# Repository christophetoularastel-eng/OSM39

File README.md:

# OSM39

*English version below.*

Un ordinateur 8 bits fait maison autour d'un **Hitachi HD6309** à
1,8432 MHz, avec son système complet : un BIOS de 8 Ko en EPROM, un
bureau graphique en mode texte (OSM-VISION) et des programmes chargés
depuis une carte SD formatée dans un système de fichiers maison (OSMFS).

## Ce qu'il y a dedans

- **128 Ko de RAM** en 4 pages de 32 Ko, **vidéo 80 × 30** caractères
  (68B45, sortie VGA 640 × 480, 8 couleurs, police en EPROM avec une page
  de semi-graphiques), **clavier PS/2**, **carte SD** (SPI matériel),
  **son AY-3-8910** et 6840, **liaison série** 115200 bauds.
- **Logiciel** (tout en assembleur 6309) :
  - le BIOS : démarrage automatique depuis la carte SD, système de
    fichiers OSMFS avec dossiers, console, clavier, son, appels entre pages ;
  - OSM-VISION : gestionnaire de fichiers à fenêtres, menus, Terminal ;
    il se pilote aussi à la « Clouris », une souris tactile à clous ;
  - des applications : EDIT (éditeur façon WordStar), CALC (tableur façon
    VisiCalc), MINITEL (terminal Vidéotex, jusqu'à MiniPavi par un vrai
    modem), PAROLE (synthèse vocale en français), un lecteur de musique
    pour l'AY, et des jeux : GLOUTON, ENVAHIS, BRIQUES, DONJON39 (un
    labyrinthe en 3D) ;
  - un assembleur 6309 qui tourne sur la machine (sa sortie est identique,
    octet pour octet, à celle de lwasm), un FORTH, un SHELL et ses commandes ;
  - des outils PC : préparation de la carte SD (`tools/egofs`), pilotage
    à distance par la liaison série (`tools/tele`), simulations logiques
    des cartes à partir de leurs netlists KiCad.
- **Un manuel de l'utilisateur** : `docs/manuel/` (le PDF est joint aux
  versions publiées, voir « Releases »).

## État du matériel

- **Ce qui tourne aujourd'hui** est la version à plusieurs cartes (carte
  CPU, carte vidéo CRT2, carte SD-clavier-son) : tout le logiciel de ce
  dépôt y est essayé.
- **OSM39_mono** (`materiel/OSM39_mono`) réunit tout sur une seule carte.
  Elle est montée et **fonctionne** depuis le 15 novembre 2026, avec tout
  le logiciel (VRAM entrelacée : construire avec `mono` dans le fichier
  `CARTE`). **Deux corrections** sont nécessaires sur la carte : elles sont
  dans le schéma, mais **le circuit imprimé n'est pas encore repris** ; sur
  une carte faite avec le circuit imprimé actuel, il faut les câbler :
  1. qualifier `/8000-9FFF` par E : la porte libre U103 (74HC32, broches
     9-10 -> 8) fait « sortie de U106 (broche 4) OU ~E (U101 broche 10) »,
     et sa sortie remplace celle de U106 vers U501 (1, 2) et U517 (2, 4, 9) ;
     sans elle, de la neige dès qu'un programme tourne en RAM basse ;
  2. relier l'OE (broche 22) de l'EPROM de police U515 à la masse ; sans
     elle, les couleurs sont en avance d'une case.

## Construire le logiciel

Il faut **lwtools 4.24** (`lwasm`, `lwlink`), `objcopy` et `python3`.

```sh
make                 # BIOS, SHELL, FORTH, commandes, ASM, OSM-VISION
./deploy_sd.sh       # tout construire et vérifier, remplir dist/
```

`dist/EPROM/` contient l'image du BIOS (`osm39.bin`, 8 Ko) et la police
(`font_osm39.bin`) à graver ; `dist/SD/` et `dist/DEPLOY.md` décrivent la
carte SD. Pour l'écrire (sur une image de test d'abord, jamais sur le
mauvais périphérique !) :

```sh
python3 tools/egofs/egofs_deploy.py /dev/sdX
```

Au démarrage, le BIOS joue un petit air, affiche sa bannière et charge
OSM-VISION ; une touche dans la première seconde ouvre le moniteur de
secours (chargement Intel hex par la liaison série).

## Les vérificateurs

Le dossier `test/` contient des vérificateurs qui font tourner les vrais
binaires dans un émulateur 6309 (avec la carte SD, le clavier, l'AY... en
modèles) et les comparent à des modèles exacts en Python :

```sh
make -C test bureau      # OSM-VISION au clavier et à la Clouris
make -C test donjon39    # le rendu 3D comparé au modèle
make -C test minitel     # le décodeur Vidéotex et le protocole PCE
```

`AGENTS.md` est la documentation technique de référence (en anglais), et
`docs/memory-map.md` la carte mémoire.

## Ce qui n'est pas ici

- **BBC BASIC** : la machine fait tourner le portage 6809/6309 de BBC BASIC
  IV par Dominic Beesley (<https://github.com/dominicbeesley/beeb6809>).
  Ce dépôt amont n'a pas de licence : ni lui ni la couche d'adaptation
  d'OSM39 ne sont publiés ici. Le manuel en parle quand même.
- Le BASIC d'origine Microsoft (« basic69 ») non plus.
- Les modèles 3D des connecteurs et de l'alimentation (`.STEP`) : ils se
  téléchargent chez les fabricants (Amphenol 86093487313H55ELF, Amphenol
  L77HDE15SD1CH4FVGA, Recom RAC20-05SK).

## Licences

- Matériel (`materiel/`) : **CERN-OHL-S v2** (`materiel/LICENSE`).
- Logiciel : **GPL v3 ou ultérieure** (`LICENSE`).
- Manuel et documentation : **CC BY-SA 4.0** (`docs/LICENSE`).
- `tools/manuel/polices/` : les polices gardent leur licence (SIL OFL).

## Crédits

- Les captures de pages Vidéotex de `tools/minitel/*.vdt`, qui servent aux
  vérificateurs, viennent du serveur **MiniPavi** (`go.minipavi.fr`).

---

# OSM39 (English)

A home-made 8-bit computer built around a **Hitachi HD6309** at
1.8432 MHz, with its whole system: an 8 KB EPROM BIOS, a text-mode
windowed desktop (OSM-VISION) and programs loaded from an SD card
formatted with a home-made file system (OSMFS). Comments, messages and
the user manual are in French.

- **Hardware**: 128 KB RAM in four 32 KB pages, 80 × 30 text video
  (68B45, VGA output, 8 colours, EPROM font with a semigraphics page),
  PS/2 keyboard, SD card on hardware SPI, AY-3-8910 and 6840 sound,
  115200 baud serial line.
- **Software** (6309 assembly): BIOS with auto-boot and a file system
  with folders; OSM-VISION file manager; an editor, a spreadsheet, a
  Videotex terminal, French text-to-speech, an AY music player, games; a
  native 6309 assembler (byte-identical to lwasm), FORTH, a shell; PC
  tools to build the SD card, drive the machine over the serial line and
  simulate the boards from their KiCad netlists.
- **Status**: the software runs on the multi-board machine (CPU, CRT2
  video, SD-keyboard-sound) and, since 2026-11-15, on **OSM39_mono**, the
  single-board version in `materiel/OSM39_mono` (build with `mono` in the
  `CARTE` file). Two fixes are in its schematic but **not yet in the PCB**:
  wire them on a board made from the current PCB (qualify `/8000-9FFF`
  with E through the spare U103 gate; tie the font EEPROM U515 OE to
  ground). Details above, in French.
- **Build**: lwtools 4.24, `objcopy`, `python3`; `make`, then
  `./deploy_sd.sh` fills `dist/` (EPROM images, SD card contents).
  `make -C test <name>` runs the verifiers (real binaries in a 6309
  emulator, compared with exact Python models).
- **Not included**: BBC BASIC (Dominic Beesley's 6809 port has no
  licence) and the Microsoft-derived BASIC; vendor 3D models.
- **Licences**: hardware CERN-OHL-S v2, software GPL v3 or later,
  documentation CC BY-SA 4.0.

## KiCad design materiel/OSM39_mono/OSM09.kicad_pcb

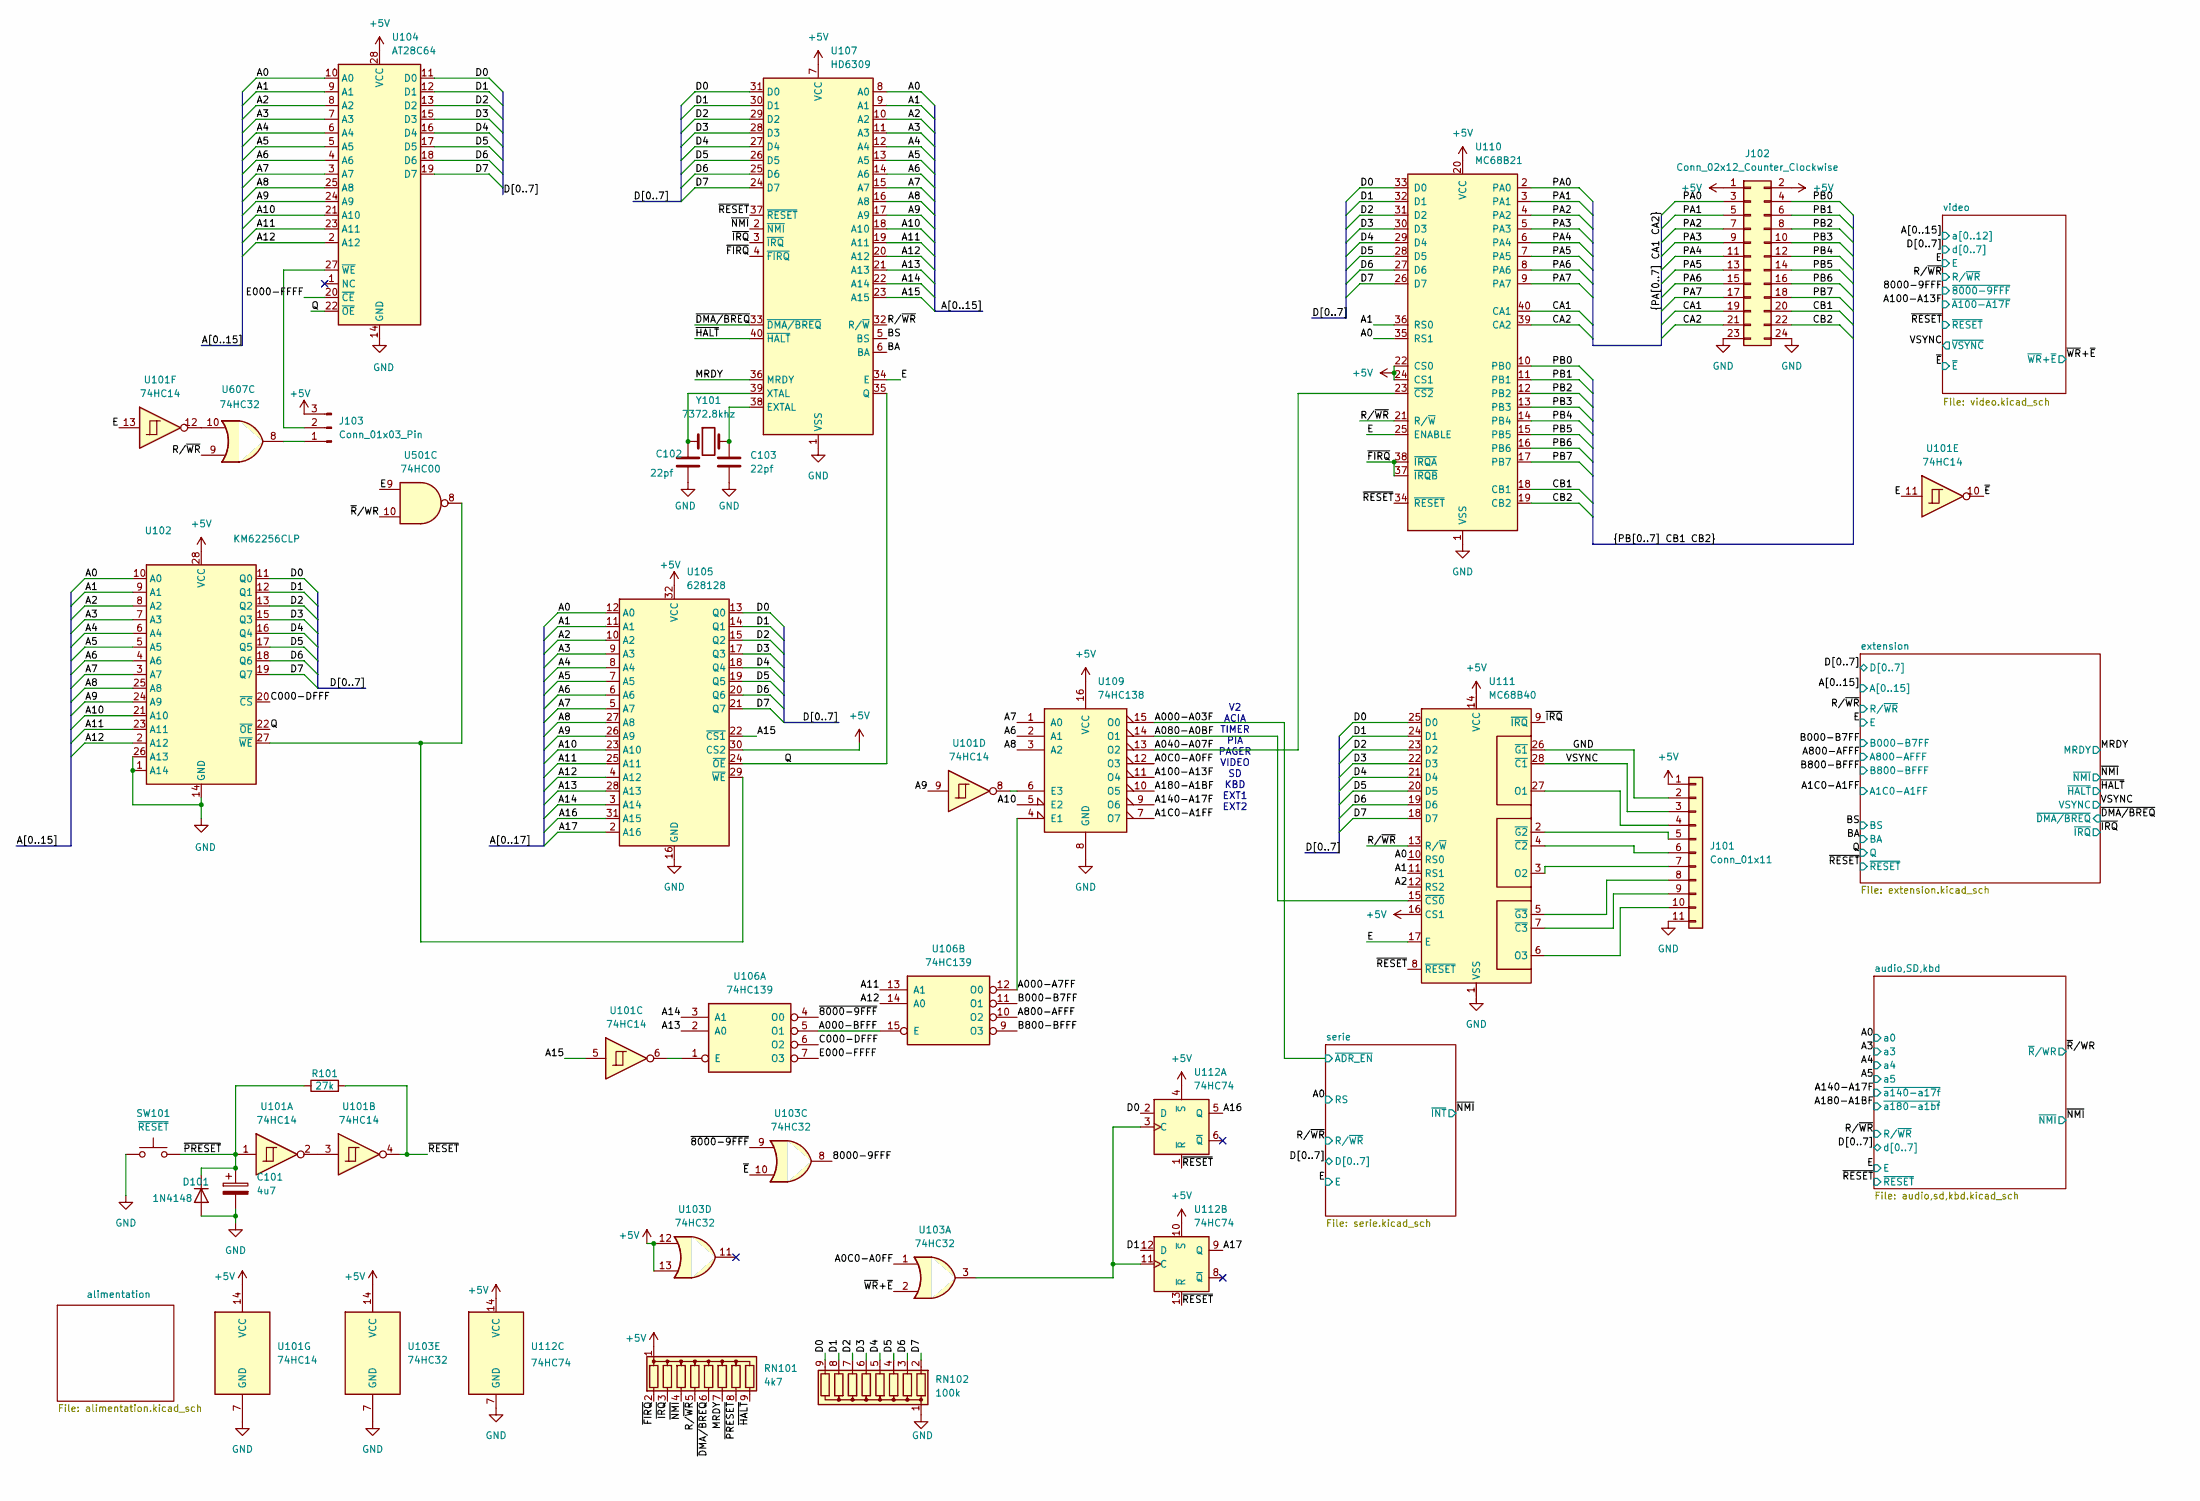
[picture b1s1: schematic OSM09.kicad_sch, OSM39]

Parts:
C101: 4u7; CP_Radial_D4.0mm_P1.50mm
C102, C103: 22pf; C_Disc_D5.0mm_W2.5mm_P2.50mm
D101: 1N4148; D_DO-35_SOD27_P7.62mm_Horizontal
J101: Conn_01x11; PinHeader_1x11_P2.54mm_Vertical
J102: Conn_02x12_Counter_Clockwise; PinHeader_2x12_P2.54mm_Vertical
J103: Conn_01x03_Pin; PinHeader_1x03_P2.54mm_Vertical
R101: 27k; R_Axial_DIN0204_L3.6mm_D1.6mm_P7.62mm_Horizontal
RN101: 4k7; R_Array_SIP9
RN102: 100k; R_Array_SIP9
SW101: ~{RESET}; SW_PUSH_6mm
U101: 74HC14; DIP-14_W7.62mm_LongPads
U102: KM62256CLP; DIP-28_W15.24mm_LongPads
U103, U607: 74HC32; DIP-14_W7.62mm_LongPads
U104: AT28C64; DIP-28_W15.24mm_LongPads
U105: 628128; DIP-32_W15.24mm_LongPads
U106: 74HC139; DIP-16_W7.62mm_LongPads
U107: HD6309; DIP-40_W15.24mm_LongPads
U109: 74HC138; DIP-16_W7.62mm_LongPads
U110: MC68B21; DIP-40_W15.24mm_LongPads
U111: MC68B40; DIP-28_W15.24mm_LongPads
U112: 74HC74; DIP-14_W7.62mm_LongPads
U501: 74HC00; DIP-14_W7.62mm_LongPads
Y101: 7372.8khz; Crystal_HC49-U_Vertical

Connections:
+5V: J101.1, J102.1, J102.2, J103.3, RN101.1 (common), U101.14 (VCC), U102.28 (VCC), U103.12, U103.13, U103.14 (VCC), U104.28 (VCC), U105.30 (CS2), U105.32 (VCC), U107.7 (VCC), U109.16 (VCC), U110.20 (VCC), U110.22 (CS0), U110.24 (CS1), U111.14 (VCC), U111.16 (CS1), U112.4 (~S), U112.10 (~S), U112.14 (VCC); also elsewhere on the board
/8000-9FFF: U103.8; also elsewhere on the board
/A0: U102.10 (A0), U104.10 (A0), U105.12 (A0), U107.8 (A0), U110.35 (RS1), U111.10 (RS0); also elsewhere on the board
/A000-A03F: U109.15 (O0); also elsewhere on the board
/A000-A7FF: U106.12 (O0), U109.4 (E1)
/A000-BFFF: U106.5 (O1), U106.15 (E)
/A0C0-A0FF: U103.1, U109.12 (O3)
/A1: U102.9 (A1), U104.9 (A1), U105.11 (A1), U107.9 (A1), U110.36 (RS0), U111.11 (RS1); also elsewhere on the board
/A1C0-A1FF: U109.7 (O7); also elsewhere on the board
/A2: U102.8 (A2), U104.8 (A2), U105.10 (A2), U107.10 (A2), U111.12 (RS2); also elsewhere on the board
/A3: U102.7 (A3), U104.7 (A3), U105.9 (A3), U107.11 (A3); also elsewhere on the board
/A4: U102.6 (A4), U104.6 (A4), U105.8 (A4), U107.12 (A4); also elsewhere on the board
/A5: U102.5 (A5), U104.5 (A5), U105.7 (A5), U107.13 (A5); also elsewhere on the board
/A6: U102.4 (A6), U104.4 (A6), U105.6 (A6), U107.14 (A6), U109.2 (A1); also elsewhere on the board
/A7: U102.3 (A7), U104.3 (A7), U105.5 (A7), U107.15 (A7), U109.1 (A0); also elsewhere on the board
/A8: U102.25 (A8), U104.25 (A8), U105.27 (A8), U107.16 (A8), U109.3 (A2); also elsewhere on the board
/A9: U101.9, U102.24 (A9), U104.24 (A9), U105.26 (A9), U107.17 (A9); also elsewhere on the board
/A10: U102.21 (A10), U104.21 (A10), U105.23 (A10), U107.18 (A10), U109.5 (E2); also elsewhere on the board
/A11: U102.23 (A11), U104.23 (A11), U105.25 (A11), U106.13 (A1), U107.19 (A11); also elsewhere on the board
/A12: U102.2 (A12), U104.2 (A12), U105.4 (A12), U106.14 (A0), U107.20 (A12); also elsewhere on the board
/A13: U105.28 (A13), U106.2 (A0), U107.21 (A13)
/A14: U105.3 (A14), U106.3 (A1), U107.22 (A14)
/A15: U101.5, U105.22 (~CS1), U107.23 (A15)
/A16: U105.31 (A15), U112.5 (Q)
/A17: U105.2 (A16), U112.9 (Q)
/A040-A07F: U109.13 (O2), U110.23 (~CS2)
/A080-A0BF: U109.14 (O1), U111.15 (~CS0)
/A100-A13F: U109.11 (O4); also elsewhere on the board
/A140-A17F: U109.9 (O6); also elsewhere on the board
/A180-A1BF: U109.10 (O5); also elsewhere on the board
/A800-AFFF: U106.10 (O2); also elsewhere on the board
/B000-B7FF: U106.11 (O1); also elsewhere on the board
/B800-BFFF: U106.9 (O3); also elsewhere on the board
/BA: U107.6 (BA); also elsewhere on the board
/BS: U107.5 (BS); also elsewhere on the board
/C000-DFFF: U102.20 (~CS), U106.6 (O2)
/CA1: J102.19, U110.40 (CA1)
/CA2: J102.21, U110.39 (CA2)
/CB1: J102.20, U110.18 (CB1)
/CB2: J102.22, U110.19 (CB2)
/D0: RN102.9 (R8), U102.11 (Q0), U104.11 (D0), U105.13 (Q0), U107.31 (D0), U110.33 (D0), U111.25 (D0), U112.2 (D); also elsewhere on the board
/D1: RN102.8 (R7), U102.12 (Q1), U104.12 (D1), U105.14 (Q1), U107.30 (D1), U110.32 (D1), U111.24 (D1), U112.12 (D); also elsewhere on the board
/D2: RN102.7 (R6), U102.13 (Q2), U104.13 (D2), U105.15 (Q2), U107.29 (D2), U110.31 (D2), U111.23 (D2); also elsewhere on the board
/D3: RN102.6 (R5), U102.15 (Q3), U104.15 (D3), U105.17 (Q3), U107.28 (D3), U110.30 (D3), U111.22 (D3); also elsewhere on the board
/D4: RN102.5 (R4), U102.16 (Q4), U104.16 (D4), U105.18 (Q4), U107.27 (D4), U110.29 (D4), U111.21 (D4); also elsewhere on the board
/D5: RN102.4 (R3), U102.17 (Q5), U104.17 (D5), U105.19 (Q5), U107.26 (D5), U110.28 (D5), U111.20 (D5); also elsewhere on the board
/D6: RN102.3 (R2), U102.18 (Q6), U104.18 (D6), U105.20 (Q6), U107.25 (D6), U110.27 (D6), U111.19 (D6); also elsewhere on the board
/D7: RN102.2 (R1), U102.19 (Q7), U104.19 (D7), U105.21 (Q7), U107.24 (D7), U110.26 (D7), U111.18 (D7); also elsewhere on the board
/E: U101.11, U101.13, U107.34 (E), U110.25 (ENABLE), U111.17 (E), U501.9; also elsewhere on the board
/E000-FFFF: U104.20 (~CE), U106.7 (O3)
/MRDY: RN101.7 (R6), U107.36 (MRDY); also elsewhere on the board
/PA0: J102.3, U110.2 (PA0)
/PA1: J102.5, U110.3 (PA1)
/PA2: J102.7, U110.4 (PA2)
/PA3: J102.9, U110.5 (PA3)
/PA4: J102.11, U110.6 (PA4)
/PA5: J102.13, U110.7 (PA5)
/PA6: J102.15, U110.8 (PA6)
/PA7: J102.17, U110.9 (PA7)
/PB0: J102.4, U110.10 (PB0)
/PB1: J102.6, U110.11 (PB1)
/PB2: J102.8, U110.12 (PB2)
/PB3: J102.10, U110.13 (PB3)
/PB4: J102.12, U110.14 (PB4)
/PB5: J102.14, U110.15 (PB5)
/PB6: J102.16, U110.16 (PB6)
/PB7: J102.18, U110.17 (PB7)
/Q: U102.22 (~OE), U104.22 (~OE), U105.24 (~OE), U107.35 (Q); also elsewhere on the board
/R/~WR: RN101.5 (R4), U107.32 (R/~W), U110.21 (R/~W), U111.13 (R/~W), U607.9; also elsewhere on the board
/VSYNC: J101.3, U111.28 (~C1); also elsewhere on the board
/~8000-9FFF: U103.9, U106.4 (O0)
/~DMA/BREQ: RN101.6 (R5), U107.33 (~DMA/BREQ); also elsewhere on the board
/~E: U101.10, U103.10; also elsewhere on the board
/~FIRQ: RN101.2 (R1), U107.4 (~FIRQ), U110.37 (~IRQB), U110.38 (~IRQA)
/~HALT: RN101.9 (R8), U107.40 (~HALT); also elsewhere on the board
/~IRQ: RN101.3 (R2), U107.3 (~IRQ), U111.9 (~IRQ); also elsewhere on the board
/~NMI: RN101.4 (R3), U107.2 (~NMI); also elsewhere on the board
/~PRESET: C101.1, D101.1 (K), R101.1, RN101.8 (R7), SW101.2, U101.1
/~RESET: R101.2, U101.4, U107.37 (~RESET), U110.34 (~RESET), U111.8 (~RESET), U112.1 (~R), U112.13 (~R); also elsewhere on the board
/~R/WR: U501.10; also elsewhere on the board
/~WR+~E: U103.2; also elsewhere on the board
GND: C101.2, C102.2, C103.2, D101.2 (A), J101.2, J101.11, J102.23, J102.24, RN102.1 (common), SW101.1, U101.7 (GND), U102.1 (A14), U102.14 (GND), U102.26 (A13), U103.7 (GND), U104.14 (GND), U105.16 (GND), U107.1 (VSS), U109.8 (GND), U110.1 (VSS), U111.1 (VSS), U111.26 (~G1), U112.7 (GND); also elsewhere on the board
unnamed: J101.4, U111.27 (O1)
unnamed: J101.5, U111.2 (~G2)
unnamed: J101.6, U111.4 (~C2)
unnamed: J101.7, U111.3 (O2)
unnamed: J101.8, U111.5 (~G3)
unnamed: J101.9, U111.7 (~C3)
unnamed: J101.10, U111.6 (O3)
unnamed: J103.1, U607.8
unnamed: J103.2, U104.27 (~WE)
unnamed: U101.2, U101.3
unnamed: U101.12, U607.10
unnamed: U102.27 (~WE), U105.29 (~WE), U501.8
unnamed: U101.6, U106.1 (E)
unnamed: C103.1, U107.38 (EXTAL), Y101.2
unnamed: C102.1, U107.39 (XTAL), Y101.1
unnamed: U101.8, U109.6 (E3)
unnamed: U103.3, U112.3 (C), U112.11 (C)

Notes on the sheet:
V2 ACIA TIMER PIA PAGER VIDEO SD KBD EXT1 EXT2

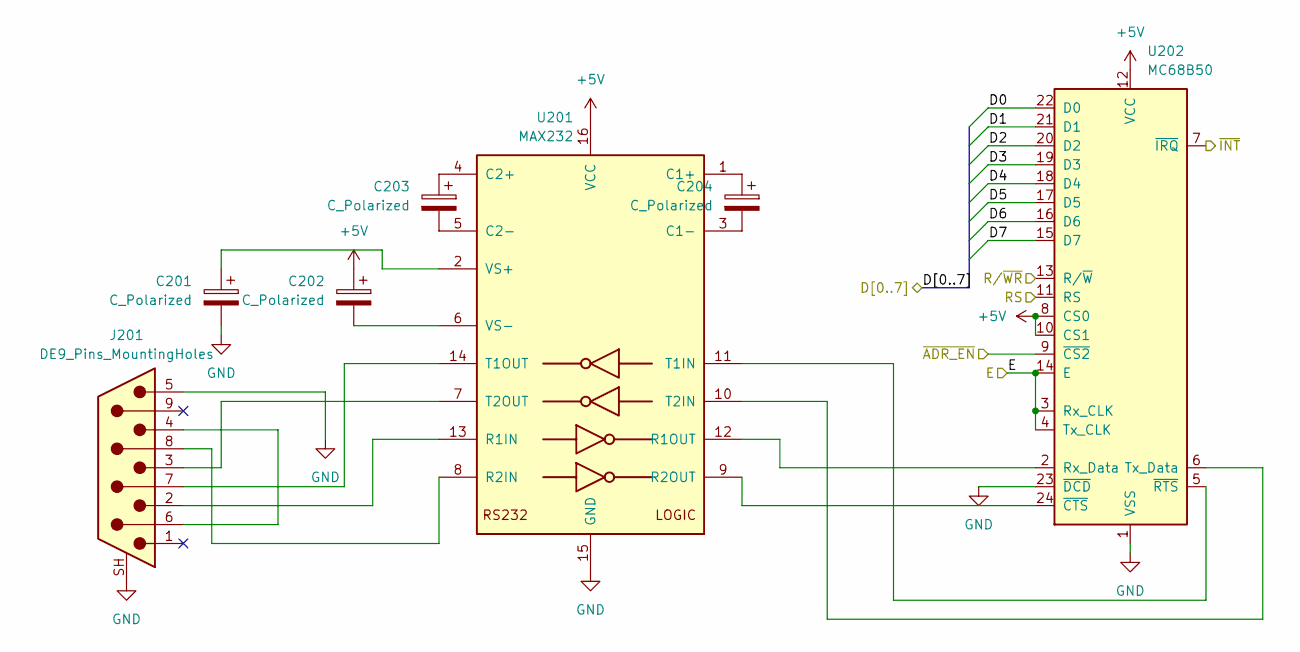
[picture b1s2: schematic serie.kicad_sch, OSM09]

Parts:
C201, C202, C203, C204: C_Polarized; CP_Radial_D4.0mm_P1.50mm
J201: DE9_Pins_MountingHoles; DSUB-9_Pins_Horizontal_P2.77x2.84mm_EdgePinOffset4.94mm_Hou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
U201: MAX232; DIP-16_W7.62mm_LongPads
U202: MC68B50; DIP-24_W15.24mm_LongPads

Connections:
+5V: C202.1, U201.16 (VCC), U202.8 (CS0), U202.10 (CS1), U202.12 (VCC); also elsewhere on the board
/A0: U202.11 (RS); also elsewhere on the board
/A000-A03F: U202.9 (~CS2); also elsewhere on the board
/D0: U202.22 (D0); also elsewhere on the board
/D1: U202.21 (D1); also elsewhere on the board
/D2: U202.20 (D2); also elsewhere on the board
/D3: U202.19 (D3); also elsewhere on the board
/D4: U202.18 (D4); also elsewhere on the board
/D5: U202.17 (D5); also elsewhere on the board
/D6: U202.16 (D6); also elsewhere on the board
/D7: U202.15 (D7); also elsewhere on the board
/E: U202.3 (Rx_CLK), U202.4 (Tx_CLK), U202.14 (E); also elsewhere on the board
/R/~WR: U202.13 (R/~W); also elsewhere on the board
/~NMI: U202.7 (~IRQ); also elsewhere on the board
GND: C201.2, J201.5, J201.SH (PAD), U201.15 (GND), U202.1 (VSS), U202.23 (~DCD); also elsewhere on the board
unnamed: J201.4, J201.6
unnamed: C204.1, U201.1 (C1+)
unnamed: C204.2, U201.3 (C1-)
unnamed: C203.1, U201.4 (C2+)
unnamed: C203.2, U201.5 (C2-)
unnamed: J201.2, U201.13 (R1IN)
unnamed: U201.12 (R1OUT), U202.2 (Rx_Data)
unnamed: J201.8, U201.8 (R2IN)
unnamed: U201.9 (R2OUT), U202.24 (~CTS)
unnamed: U201.11 (T1IN), U202.5 (~RTS)
unnamed: J201.7, U201.14 (T1OUT)
unnamed: U201.10 (T2IN), U202.6 (Tx_Data)
unnamed: J201.3, U201.7 (T2OUT)
unnamed: C201.1, U201.2 (VS+)
unnamed: C202.2, U201.6 (VS-)

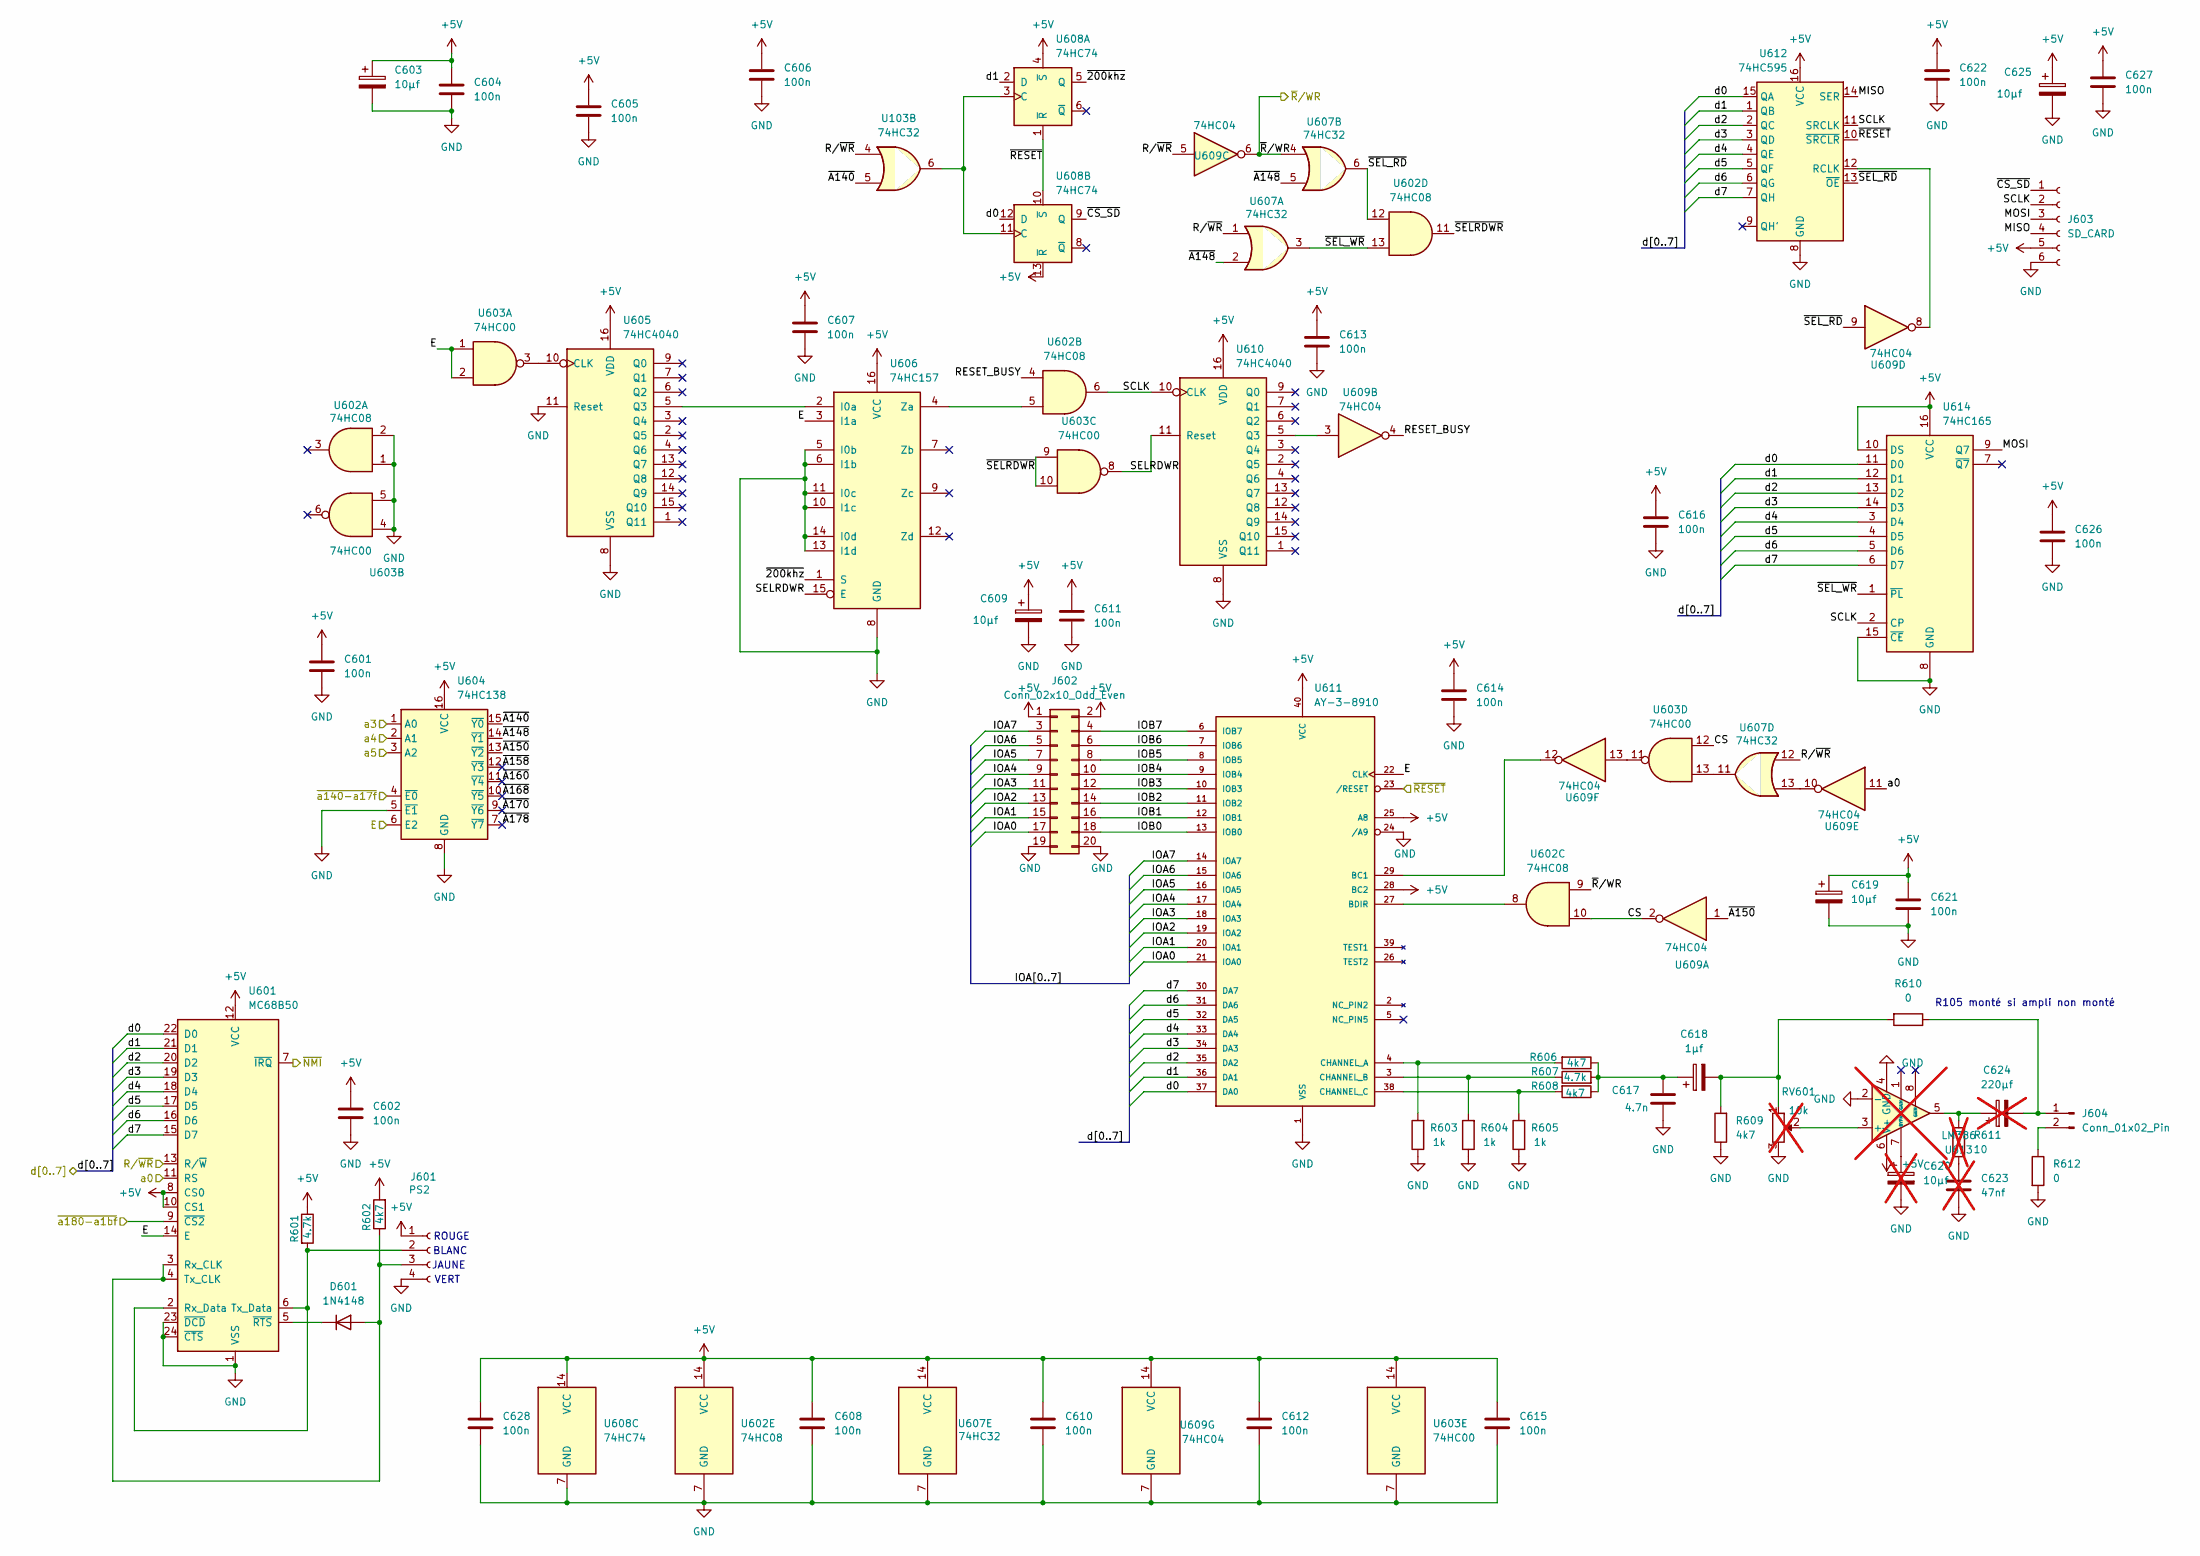
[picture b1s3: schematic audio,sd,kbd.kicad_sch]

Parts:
C601, C602, C604, C605, C606, C607, C608, C610, C611, C612, C613, C614, C615, C616, C621, C622, C626, C627, C628: 100n; C_Disc_D5.0mm_W2.5mm_P2.50mm
C603, C609, C619, C625: 10µf; C_Radial_D5.0mm_H5.0mm_P2.00mm
C617: 4.7n; C_Disc_D5.0mm_W2.5mm_P2.50mm
C618: 1µf; C_Radial_D5.0mm_H5.0mm_P2.00mm
C620: 10µf; C_Radial_D5.0mm_H5.0mm_P2.00mm; not fitted
C623: 47nf; C_Disc_D5.0mm_W2.5mm_P2.50mm; not fitted
C624: 220µf; C_Radial_D5.0mm_H5.0mm_P2.00mm; not fitted
D601: 1N4148; D_DO-35_SOD27_P7.62mm_Horizontal
J601: PS2; PinHeader_1x04_P2.54mm_Vertical
J602: Conn_02x10_Odd_Even; PinHeader_2x10_P2.54mm_Vertical
J603: SD_CARD; PinSocket_1x06_P2.54mm_Horizontal
J604: Conn_01x02_Pin; PinHeader_1x02_P2.54mm_Vertical
R601, R607: 4.7k; R_Axial_DIN0207_L6.3mm_D2.5mm_P7.62mm_Horizontal
R602, R606, R608, R609: 4k7; R_Axial_DIN0207_L6.3mm_D2.5mm_P7.62mm_Horizontal
R603, R604, R605: 1k; R_Axial_DIN0207_L6.3mm_D2.5mm_P7.62mm_Horizontal
R610, R612: 0; R_Axial_DIN0207_L6.3mm_D2.5mm_P7.62mm_Horizontal
R611: 10; R_Axial_DIN0207_L6.3mm_D2.5mm_P7.62mm_Horizontal; not fitted
RV601: 10k; Potentiometer_ACP_CA6-H2,5_Horizontal; not fitted
U103, U607: 74HC32; DIP-14_W7.62mm_LongPads
U601: MC68B50; DIP-24_W15.24mm_LongPads
U602: 74HC08; DIP-14_W7.62mm_LongPads
U603: 74HC00; DIP-14_W7.62mm_LongPads
U604: 74HC138; DIP-16_W7.62mm_LongPads
U605, U610: 74HC4040; DIP-16_W7.62mm_LongPads
U606: 74HC157; DIP-16_W7.62mm_LongPads
U608: 74HC74; DIP-14_W7.62mm_LongPads
U609: 74HC04; DIP-14_W7.62mm_LongPads
U611: AY-3-8910; DIP-40_W15.24mm_Socket
U612: 74HC595; DIP-16_W7.62mm_LongPads
U613: LM386; DIP-8_W7.62mm_LongPads; not fitted
U614: 74HC165; DIP-16_W7.62mm_LongPads

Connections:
+5V: C601.1, C602.1, C603.1, C604.1, C605.1, C606.1, C607.1, C608.1, C609.1, C610.1, C611.1, C612.1, C613.1, C614.1, C615.1, C616.1, C619.1, C621.1, C622.1, C625.1, C626.1, C627.1, C628.1, J601.1, J602.1, J602.2, J603.5, R601.1, R602.2, U601.8 (CS0), U601.10 (CS1), U601.12 (VCC), U602.14 (VCC), U603.14 (VCC), U604.16 (VCC), U605.16 (VDD), U606.16 (VCC), U607.14 (VCC), U608.4 (~S), U608.13 (~R), U608.14 (VCC), U609.14 (VCC), U610.16 (VDD), U611.25 (A8), U611.28 (BC2), U611.40 (VCC), U612.16 (VCC), U613.6 (V+), U614.10 (DS), U614.16 (VCC); also elsewhere on the board
/A0: U601.11 (RS), U609.11; also elsewhere on the board
/A3: U604.1 (A0); also elsewhere on the board
/A4: U604.2 (A1); also elsewhere on the board
/A5: U604.3 (A2); also elsewhere on the board
/A140-A17F: U604.4 (~E0); also elsewhere on the board
/A180-A1BF: U601.9 (~CS2); also elsewhere on the board
/D0: U601.22 (D0), U608.12 (D), U611.37 (DA0), U612.15 (QA), U614.11 (D0); also elsewhere on the board
/D1: U601.21 (D1), U608.2 (D), U611.36 (DA1), U612.1 (QB), U614.12 (D1); also elsewhere on the board
/D2: U601.20 (D2), U611.35 (DA2), U612.2 (QC), U614.13 (D2); also elsewhere on the board
/D3: U601.19 (D3), U611.34 (DA3), U612.3 (QD), U614.14 (D3); also elsewhere on the board
/D4: U601.18 (D4), U611.33 (DA4), U612.4 (QE), U614.3 (D4); also elsewhere on the board
/D5: U601.17 (D5), U611.32 (DA5), U612.5 (QF), U614.4 (D5); also elsewhere on the board
/D6: U601.16 (D6), U611.31 (DA6), U612.6 (QG), U614.5 (D6); also elsewhere on the board
/D7: U601.15 (D7), U611.30 (DA7), U612.7 (QH), U614.6 (D7); also elsewhere on the board
/E: U601.14 (E), U603.1, U603.2, U604.6 (E2), U606.3 (I1a), U611.22 (CLK); also elsewhere on the board
/R/~WR: U103.4, U601.13 (R/~W), U607.1, U607.12, U609.5; also elsewhere on the board
/audio,SD,kbd/CS: U602.10, U603.12, U609.2
/audio,SD,kbd/IOA0: J602.17, U611.21 (IOA0)
/audio,SD,kbd/IOA1: J602.15, U611.20 (IOA1)
/audio,SD,kbd/IOA2: J602.13, U611.19 (IOA2)
/audio,SD,kbd/IOA3: J602.11, U611.18 (IOA3)
/audio,SD,kbd/IOA4: J602.9, U611.17 (IOA4)
/audio,SD,kbd/IOA5: J602.7, U611.16 (IOA5)
/audio,SD,kbd/IOA6: J602.5, U611.15 (IOA6)
/audio,SD,kbd/IOA7: J602.3, U611.14 (IOA7)
/audio,SD,kbd/IOB0: J602.18, U611.13 (IOB0)
/audio,SD,kbd/IOB1: J602.16, U611.12 (IOB1)
/audio,SD,kbd/IOB2: J602.14, U611.11 (IOB2)
/audio,SD,kbd/IOB3: J602.12, U611.10 (IOB3)
/audio,SD,kbd/IOB4: J602.10, U611.9 (IOB4)
/audio,SD,kbd/IOB5: J602.8, U611.8 (IOB5)
/audio,SD,kbd/IOB6: J602.6, U611.7 (IOB6)
/audio,SD,kbd/IOB7: J602.4, U611.6 (IOB7)
/audio,SD,kbd/MISO: J603.4, U612.14 (SER)
/audio,SD,kbd/MOSI: J603.3, U614.9 (Q7)
/audio,SD,kbd/RESET_BUSY: U602.4, U609.4
/audio,SD,kbd/SCLK: J603.2, U602.6, U610.10 (CLK), U612.11 (SRCLK), U614.2 (CP)
/audio,SD,kbd/SELRDWR: U603.8, U606.15 (E), U610.11 (Reset)
/audio,SD,kbd/~200khz: U606.1 (S), U608.5 (Q)
/audio,SD,kbd/~A140: U103.5, U604.15 (~Y0)
/audio,SD,kbd/~A148: U604.14 (~Y1), U607.2, U607.5
/audio,SD,kbd/~A150: U604.13 (~Y2), U609.1
/audio,SD,kbd/~A158: U604.12 (~Y3)
/audio,SD,kbd/~A160: U604.11 (~Y4)
/audio,SD,kbd/~A168: U604.10 (~Y5)
/audio,SD,kbd/~A170: U604.9 (~Y6)
/audio,SD,kbd/~A178: U604.7 (~Y7)
/audio,SD,kbd/~CS_SD: J603.1, U608.9 (Q)
/audio,SD,kbd/~SELRDWR: U602.11, U603.9, U603.10
/audio,SD,kbd/~SEL_RD: U602.12, U607.6, U609.9, U612.13 (~OE)
/audio,SD,kbd/~SEL_WR: U602.13, U607.3, U614.1 (~PL)
/~NMI: U601.7 (~IRQ); also elsewhere on the board
/~RESET: U608.1 (~R), U608.10 (~S), U611.23 (/RESET), U612.10 (~SRCLR); also elsewhere on the board
/~R/WR: U602.9, U607.4, U609.6; also elsewhere on the board
GND: C601.2, C602.2, C603.2, C604.2, C605.2, C606.2, C607.2, C608.2, C609.2, C610.2, C611.2, C612.2, C613.2, C614.2, C615.2, C616.2, C617.2, C619.2, C620.2, C621.2, C622.2, C623.2, C625.2, C626.2, C627.2, C628.2, J601.4, J602.19, J602.20, J603.6, R603.1, R604.1, R605.1, R609.1, R612.2, RV601.3, U601.1 (VSS), U601.23 (~DCD), U601.24 (~CTS), U602.1, U602.2, U602.7 (GND), U603.4, U603.5, U603.7 (GND), U604.5 (~E1), U604.8 (GND), U605.8 (VSS), U605.11 (Reset), U606.5 (I0b), U606.6 (I1b), U606.8 (GND), U606.10 (I1c), U606.11 (I0c), U606.13 (I1d), U606.14 (I0d), U607.7 (GND), U608.7 (GND), U609.7 (GND), U610.8 (VSS), U611.1 (VSS), U611.24 (/A9), U612.8 (GND), U613.2 (-), U613.4 (GND), U614.8 (GND), U614.15 (~CE); also elsewhere on the board
unnamed: C617.1, C618.1, R606.1, R607.2, R608.1
unnamed: C618.2, R609.2, R610.2, RV601.1
unnamed: C623.1, R611.1
unnamed: C624.1, R611.2, U613.5
unnamed: D601.2 (A), J601.3, R602.1, U601.3 (Rx_CLK), U601.4 (Tx_CLK)
unnamed: D601.1 (K), U601.5 (~RTS)
unnamed: J601.2, R601.2, U601.2 (Rx_Data), U601.6 (Tx_Data)
unnamed: C624.2, J604.1, R610.1
unnamed: J604.2, R612.1
unnamed: U603.11, U609.13
unnamed: U603.13, U607.11
unnamed: U603.3, U605.10 (CLK)
unnamed: U605.5 (Q3), U606.2 (I0a)
unnamed: U602.5, U606.4 (Za)
unnamed: U607.13, U609.10
unnamed: U103.6, U608.3 (C), U608.11 (C)
unnamed: U609.3, U610.5 (Q3)
unnamed: U609.12, U611.29 (BC1)
unnamed: U602.8, U611.27 (BDIR)
unnamed: R603.2, R606.2, U611.4 (CHANNEL_A)
unnamed: R604.2, R607.1, U611.3 (CHANNEL_B)
unnamed: R605.2, R608.2, U611.38 (CHANNEL_C)
unnamed: U609.8, U612.12 (RCLK)
unnamed: RV601.2, U613.3 (+)
unnamed: C620.1, U613.7 (BYPASS)

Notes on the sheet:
R105 monté si ampli non monté
JAUNE
VERT
BLANC
ROUGE
